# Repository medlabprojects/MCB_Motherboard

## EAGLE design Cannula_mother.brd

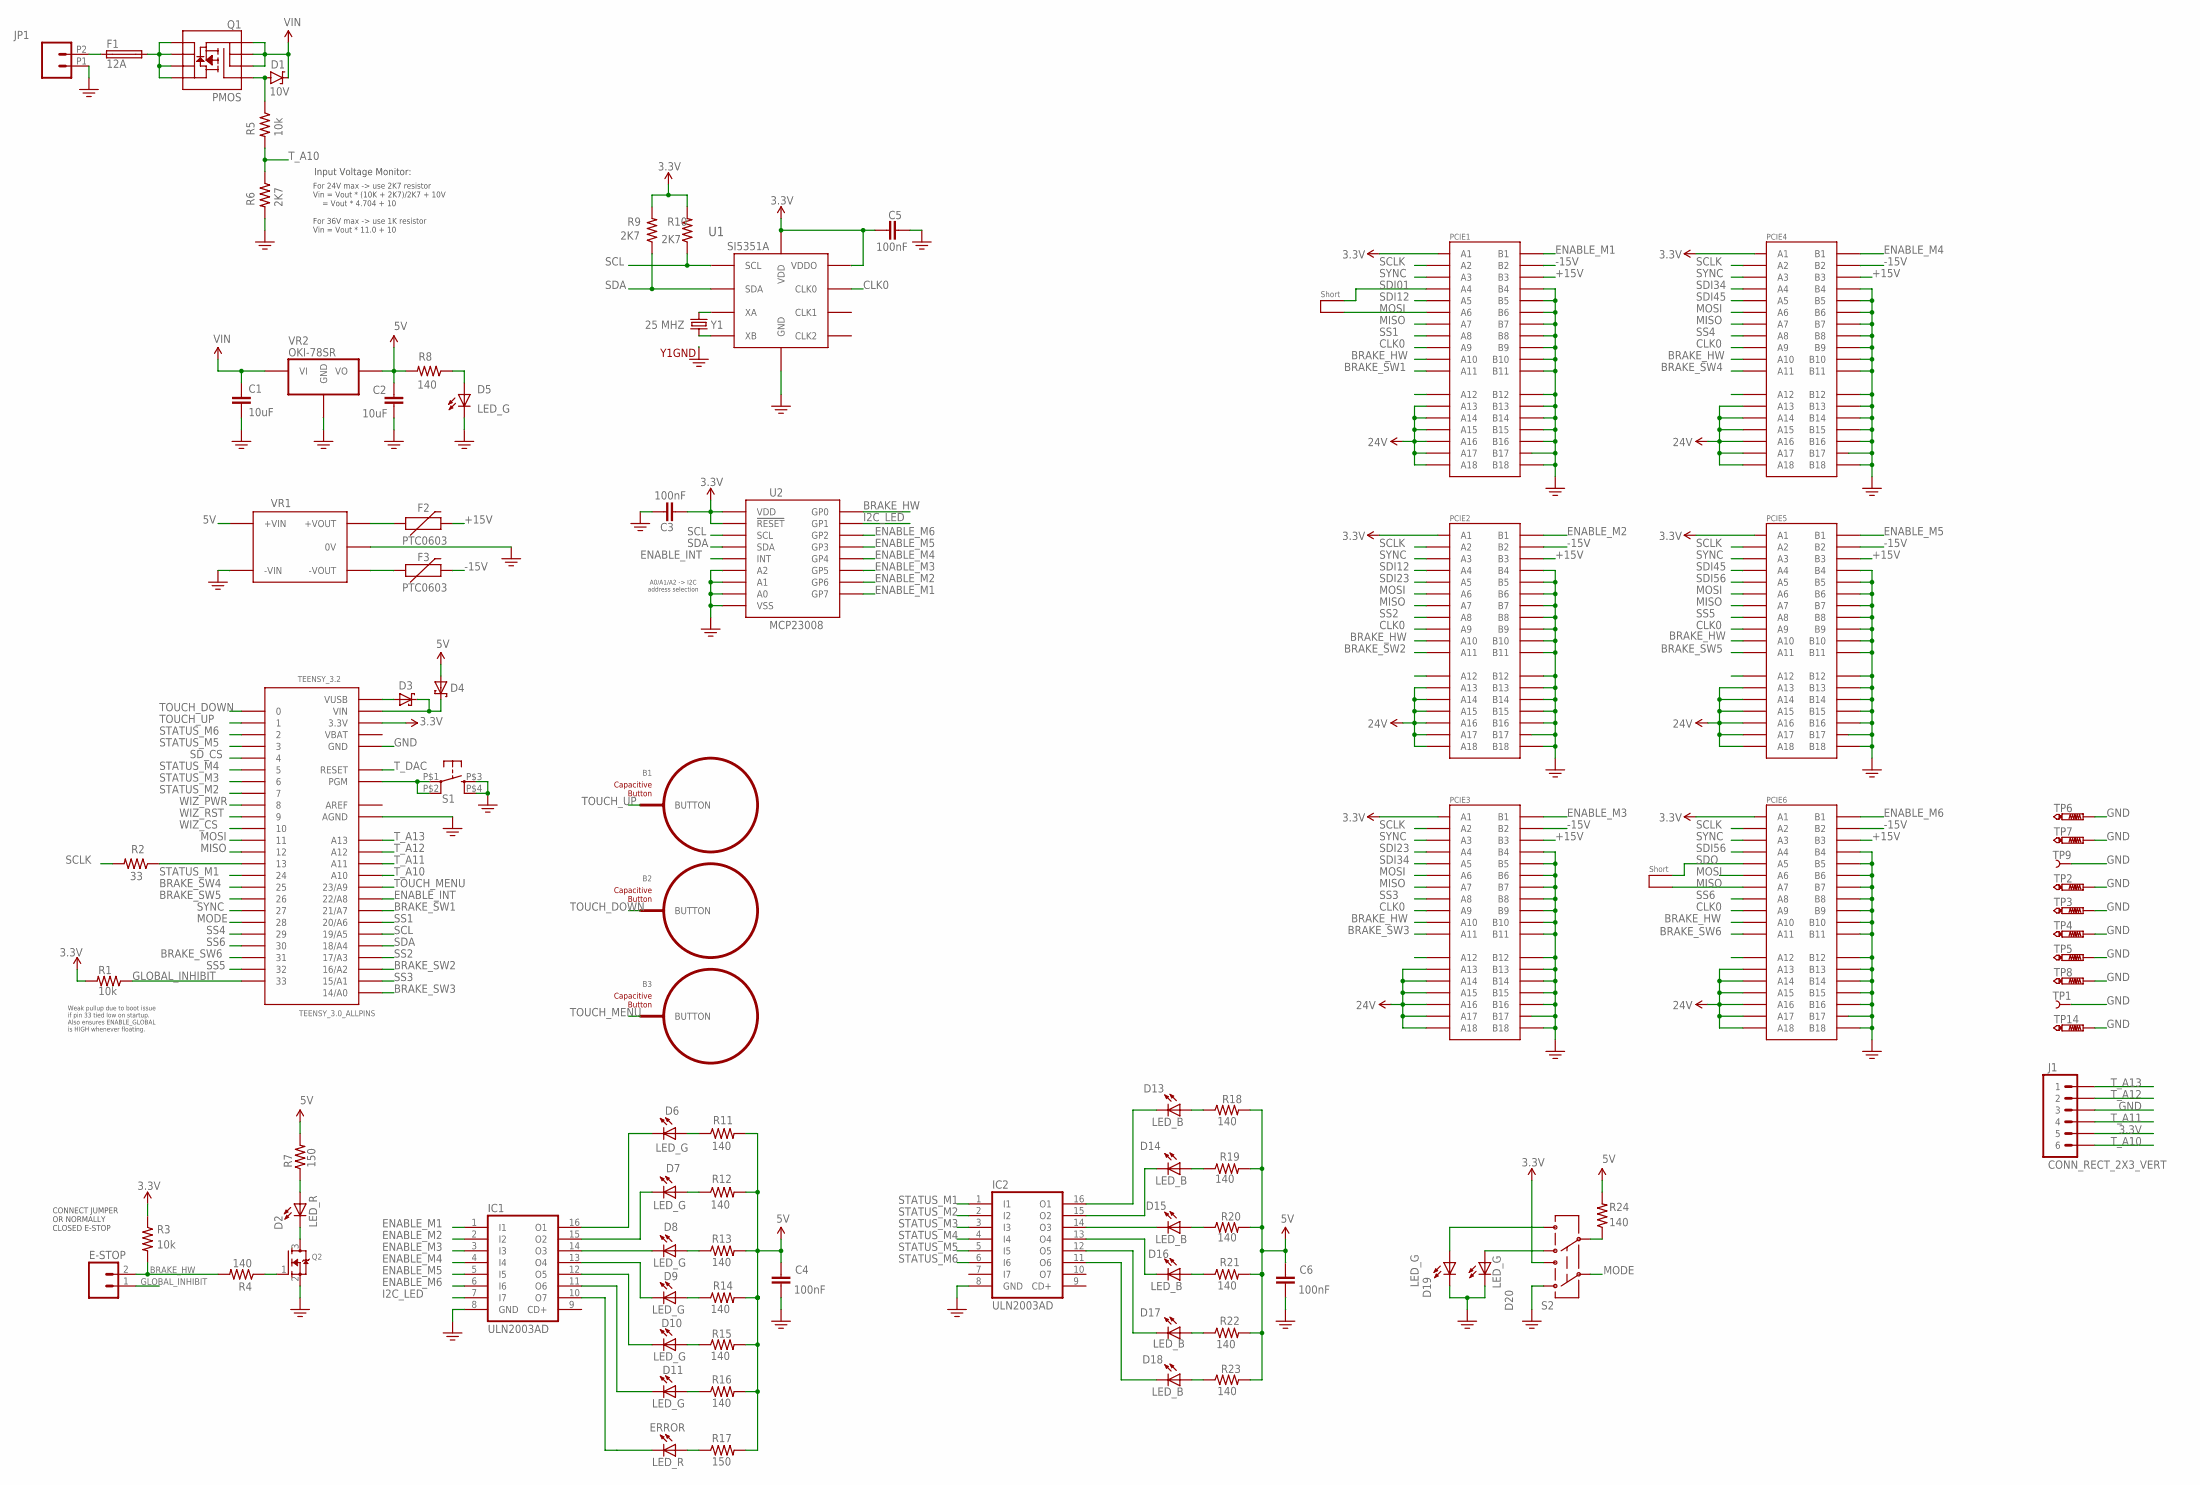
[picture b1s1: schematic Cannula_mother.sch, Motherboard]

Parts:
B1, B2: BUTTON_PASSIVE-8MM-ARROW; BUTTON_PASSIVE_8MM_UP
B3: BUTTON_PASSIVE-8MM-MENU; BUTTON_PASSIVE_8MM_MENU
C1, C2: 10uF; 1210
C3, C4, C5, C6: 100nF; 0603-CAP
D1: 10V; SOD-323
D2: LED_R; LED-0805
D3, D4: DIODE-POWERDI123; POWERDI123
D5, D6, D7, D8, D9, D10, D11, D19, D20: LED_G; LED-0805
D13, D14, D15, D16, D17, D18: LED_B; LED-0805
E-STOP: M02LOCK; 1X02_LOCK
ERROR: LED_R; LED-0805
F1: 12A; 1206
F2, F3: PTC0603; 0603
IC1, IC2: ULN2003AD; SO16
J1: CONN_RECT_2X3_VERT; 2X3
JP1: M026.35MM_SCREWTERM; 1X02_6.35_SCREWTERM
JP3, JP4: SHORT
PCIE1, PCIE2, PCIE3, PCIE4, PCIE5, PCIE6: PCIE-36-SKT
Q1: PMOS; SO08
Q2: MOSFET-NREFLOW; SOT23
R1, R3, R5: 10k; 0603-RES
R2: 33; 0603-RES
R4, R8, R11, R12, R13, R14, R15, R16, R18, R19, R20, R21, R22, R23, R24: 140; 0603-RES
R6, R9, R10: 2K7; 0603-RES
R7, R17: 150; 0603-RES
S1: SWITCH-TACT; LS38
S2: SWITCH-DPDT-SLIDER-SMD; JS202011SCQN
TEENSY_3.2: TEENSY_3.0_ALLPINS
TP1, TP9: TEST-POINT_5021
TP2, TP3, TP4, TP5, TP6, TP7, TP8, TP14: PTR1TP20R; TP20R
U1: SI5351A; MSOP10
U2: MCP23008; SSOP20
VR1: DCDC_IA_SERIES0515S; DCDC_IA_SERIES
VR2: OKI-78SR
Y1: 25 MHZ; CX3225SB

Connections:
3.3V: C3.1, C5.1, J1.5, PCIE1.A1, PCIE2.A1, PCIE3.A1, PCIE4.A1, PCIE5.A1, PCIE6.A1, R1.2, R3.1, R9.2, R10.2, S2.3, TEENSY_3.2.3.3V, TEENSY_3.2.3.3V1 (3.3V), TEENSY_3.2.3.3V2 (3.3V), U1.1 (VDD), U1.7 (VDDO), U2.6 (!RESET), U2.20 (VDD)
5V: C2.1, C4.1, C6.1, D4.P$2 (A), R7.2, R8.2, R11.2, R12.2, R13.2, R14.2, R15.2, R16.2, R17.2, R18.2, R19.2, R20.2, R21.2, R22.2, R23.2, R24.2, VR1.+VIN, VR2.P$3 (VO)
+15V: F2.2, PCIE1.B3, PCIE2.B3, PCIE3.B3, PCIE4.B3, PCIE5.B3, PCIE6.B3
-15V: F3.2, PCIE1.B2, PCIE2.B2, PCIE3.B2, PCIE4.B2, PCIE5.B2, PCIE6.B2
AREF: TEENSY_3.2.AREF
B: Q2.1 (G), R4.1
BRAKE_HW: E-STOP.2, PCIE1.A10, PCIE2.A10, PCIE3.A10, PCIE4.A10, PCIE5.A10, PCIE6.A10, R3.2, R4.2, U2.12 (GP0)
BRAKE_SW1: PCIE1.A11, TEENSY_3.2.21/A7
BRAKE_SW2: PCIE2.A11, TEENSY_3.2.16/A2
BRAKE_SW3: PCIE3.A11, TEENSY_3.2.14/A0
BRAKE_SW4: PCIE4.A11, TEENSY_3.2.25
BRAKE_SW5: PCIE5.A11, TEENSY_3.2.26
BRAKE_SW6: PCIE6.A11, TEENSY_3.2.31
C: D2.C, Q2.3 (D)
CLK0: PCIE1.A9, PCIE2.A9, PCIE3.A9, PCIE4.A9, PCIE5.A9, PCIE6.A9, U1.10 (CLK0)
ENABLE_INT: TEENSY_3.2.22/A8, U2.8 (INT)
ENABLE_M1: IC1.1 (I1), PCIE1.B1, U2.19 (GP7)
ENABLE_M2: IC1.2 (I2), PCIE2.B1, U2.18 (GP6)
ENABLE_M3: IC1.3 (I3), PCIE3.B1, U2.17 (GP5)
ENABLE_M4: IC1.4 (I4), PCIE4.B1, U2.16 (GP4)
ENABLE_M5: IC1.5 (I5), PCIE5.B1, U2.15 (GP3)
ENABLE_M6: IC1.6 (I6), PCIE6.B1, U2.14 (GP2)
GLOBAL_INHIBIT: E-STOP.1, R1.1, TEENSY_3.2.33
GND: C1.2, C2.2, C3.2, C4.2, C5.2, C6.2, D5.C, D19.C, D20.C, IC1.8 (GND), IC2.8 (GND), J1.3, JP1.P1 (1), PCIE1.B4, PCIE1.B5, PCIE1.B6, PCIE1.B7, PCIE1.B8, PCIE1.B9, PCIE1.B10, PCIE1.B11, PCIE1.B12, PCIE1.B13, PCIE1.B14, PCIE1.B15, PCIE1.B16, PCIE1.B17, PCIE1.B18, PCIE2.B4, PCIE2.B5, PCIE2.B6, PCIE2.B7, PCIE2.B8, PCIE2.B9, PCIE2.B10, PCIE2.B11, PCIE2.B12, PCIE2.B13, PCIE2.B14, PCIE2.B15, PCIE2.B16, PCIE2.B17, PCIE2.B18, PCIE3.B4, PCIE3.B5, PCIE3.B6, PCIE3.B7, PCIE3.B8, PCIE3.B9, PCIE3.B10, PCIE3.B11, PCIE3.B12, PCIE3.B13, PCIE3.B14, PCIE3.B15, PCIE3.B16, PCIE3.B17, PCIE3.B18, PCIE4.B4, PCIE4.B5, PCIE4.B6, PCIE4.B7, PCIE4.B8, PCIE4.B9, PCIE4.B10, PCIE4.B11, PCIE4.B12, PCIE4.B13, PCIE4.B14, PCIE4.B15, PCIE4.B16, PCIE4.B17, PCIE4.B18, PCIE5.B4, PCIE5.B5, PCIE5.B6, PCIE5.B7, PCIE5.B8, PCIE5.B9, PCIE5.B10, PCIE5.B11, PCIE5.B12, PCIE5.B13, PCIE5.B14, PCIE5.B15, PCIE5.B16, PCIE5.B17, PCIE5.B18, PCIE6.B4, PCIE6.B5, PCIE6.B6, PCIE6.B7, PCIE6.B8, PCIE6.B9, PCIE6.B10, PCIE6.B11, PCIE6.B12, PCIE6.B13, PCIE6.B14, PCIE6.B15, PCIE6.B16, PCIE6.B17, PCIE6.B18, Q2.2 (S), R6.2, S1.P$3 (3), S1.P$4 (4), S2.1, TEENSY_3.2.AGND, TEENSY_3.2.GND, TEENSY_3.2.GND1 (GND), TEENSY_3.2.GND2 (GND), TP1.P$1, TP2.TP, TP3.TP, TP4.TP, TP5.TP, TP6.TP, TP7.TP, TP8.TP, TP9.P$1, TP14.TP, U1.8 (GND), U2.3 (A2), U2.4 (A1), U2.5 (A0), U2.9 (VSS), VR1.0V, VR1.-VIN, VR2.P$2 (GND), Y1.GND@1 (GND), Y1.GND@2 (GND)
I2C_LED: IC1.7 (I7), U2.13 (GP1)
MISO: JP4.P$2, PCIE1.A7, PCIE2.A7, PCIE3.A7, PCIE4.A7, PCIE5.A7, PCIE6.A7, TEENSY_3.2.12
MODE: S2.2, TEENSY_3.2.28
MOSI: JP3.P$2, PCIE1.A6, PCIE2.A6, PCIE3.A6, PCIE4.A6, PCIE5.A6, PCIE6.A6, TEENSY_3.2.11
unnamed: F2.1, VR1.+VOUT
unnamed: F3.1, VR1.-VOUT
unnamed: D8.C, IC1.14 (O3)
unnamed: D2.A, R7.1
unnamed: D1.A, Q1.4 (G), R5.1
unnamed: D15.C, IC2.14 (O3)
unnamed: F1.P$2 (2), Q1.5 (D), Q1.6 (D), Q1.7 (D), Q1.8 (D)
unnamed: D5.A, R8.1
unnamed: R24.1, S2.5
unnamed: D20.A, S2.4
unnamed: D19.A, S2.6
unnamed: ERROR.A, R17.1
unnamed: F1.P$1 (1), JP1.P2 (2)
unnamed: D17.A, R22.1
unnamed: D13.A, R18.1
unnamed: D14.A, R19.1
unnamed: D15.A, R20.1
unnamed: D16.A, R21.1
unnamed: D18.A, R23.1
unnamed: ERROR.C, IC1.10 (O7)
unnamed: D10.A, R15.1
unnamed: D6.A, R11.1
unnamed: D7.A, R12.1
unnamed: D8.A, R13.1
unnamed: D9.A, R14.1
unnamed: D11.A, R16.1
unnamed: D13.C, IC2.16 (O1)
unnamed: D14.C, IC2.15 (O2)
unnamed: D16.C, IC2.13 (O4)
unnamed: D17.C, IC2.12 (O5)
unnamed: D18.C, IC2.11 (O6)
unnamed: D7.C, IC1.15 (O2)
unnamed: D9.C, IC1.13 (O4)
unnamed: D10.C, IC1.12 (O5)
unnamed: D11.C, IC1.11 (O6)
unnamed: D6.C, IC1.16 (O1)
unnamed: R2.1, TEENSY_3.2.13
PGM: S1.P$1 (1), S1.P$2 (2), TEENSY_3.2.PGM
SCL: R10.1, TEENSY_3.2.19/A5, U1.4 (SCL), U2.1 (SCL)
SCLK: PCIE1.A2, PCIE2.A2, PCIE3.A2, PCIE4.A2, PCIE5.A2, PCIE6.A2, R2.2
SDA: R9.1, TEENSY_3.2.18/A4, U1.5 (SDA), U2.2 (SDA)
SDI01: JP3.P$1, PCIE1.A4
SDI12: PCIE1.A5, PCIE2.A4
SDI23: PCIE2.A5, PCIE3.A4
SDI34: PCIE3.A5, PCIE4.A4
SDI45: PCIE4.A5, PCIE5.A4
SDI56: PCIE5.A5, PCIE6.A4
SDO: JP4.P$1, PCIE6.A5
SD_CS: TEENSY_3.2.4
SS1: PCIE1.A8, TEENSY_3.2.20/A6
SS2: PCIE2.A8, TEENSY_3.2.17/A3
SS3: PCIE3.A8, TEENSY_3.2.15/A1
SS4: PCIE4.A8, TEENSY_3.2.29
SS5: PCIE5.A8, TEENSY_3.2.32
SS6: PCIE6.A8, TEENSY_3.2.30
STATUS_M1: IC2.1 (I1), TEENSY_3.2.24
STATUS_M2: IC2.2 (I2), TEENSY_3.2.7
STATUS_M3: IC2.3 (I3), TEENSY_3.2.6
STATUS_M4: IC2.4 (I4), TEENSY_3.2.5
STATUS_M5: IC2.5 (I5), TEENSY_3.2.3
STATUS_M6: IC2.6 (I6), TEENSY_3.2.2
SYNC: PCIE1.A3, PCIE2.A3, PCIE3.A3, PCIE4.A3, PCIE5.A3, PCIE6.A3, TEENSY_3.2.27
TOUCH_DOWN: B2.BUTTON, TEENSY_3.2.0
TOUCH_MENU: B3.BUTTON, TEENSY_3.2.23/A9
TOUCH_UP: B1.BUTTON, TEENSY_3.2.1
T_A10: J1.6, R5.2, R6.1, TEENSY_3.2.A10
T_A11: J1.4, TEENSY_3.2.A11
T_A12: J1.2, TEENSY_3.2.A12
T_A13: J1.1, TEENSY_3.2.A13
T_DAC: TEENSY_3.2.RESET
T_VIN: D3.P$1 (C), D4.P$1 (C), TEENSY_3.2.VIN
VBAT: TEENSY_3.2.VBAT
VIN: C1.1, D1.C, PCIE1.A13, PCIE1.A14, PCIE1.A15, PCIE1.A16, PCIE1.A17, PCIE1.A18, PCIE2.A13, PCIE2.A14, PCIE2.A15, PCIE2.A16, PCIE2.A17, PCIE2.A18, PCIE3.A13, PCIE3.A14, PCIE3.A15, PCIE3.A16, PCIE3.A17, PCIE3.A18, PCIE4.A13, PCIE4.A14, PCIE4.A15, PCIE4.A16, PCIE4.A17, PCIE4.A18, PCIE5.A13, PCIE5.A14, PCIE5.A15, PCIE5.A16, PCIE5.A17, PCIE5.A18, PCIE6.A13, PCIE6.A14, PCIE6.A15, PCIE6.A16, PCIE6.A17, PCIE6.A18, Q1.1 (S), Q1.2 (S), Q1.3 (S), VR2.P$1 (VI)
VUSB: D3.P$2 (A), TEENSY_3.2.VUSB
WIZ_CS: TEENSY_3.2.10
WIZ_PWR: TEENSY_3.2.8
WIZ_RST: TEENSY_3.2.9
XA: U1.2 (XA), Y1.HOT2 (2)
XB: U1.3 (XB), Y1.HOT1 (1)

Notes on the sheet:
CONNECT JUMPER OR NORMALLY CLOSED E-STOP
A0/A1/A2 -> I2C address selection
Weak pullup due to boot issue if pin 33 tied low on startup. Also ensures ENABLE_GLOBAL is HIGH whenever floating.
Input Voltage Monitor:
For 24V max -> use 2K7 resistor Vin = Vout * (10K + 2K7)/2K7 + 10V = Vout * 4.704 + 10 For 36V max -> use 1K resistor Vin = Vout * 11.0 + 10

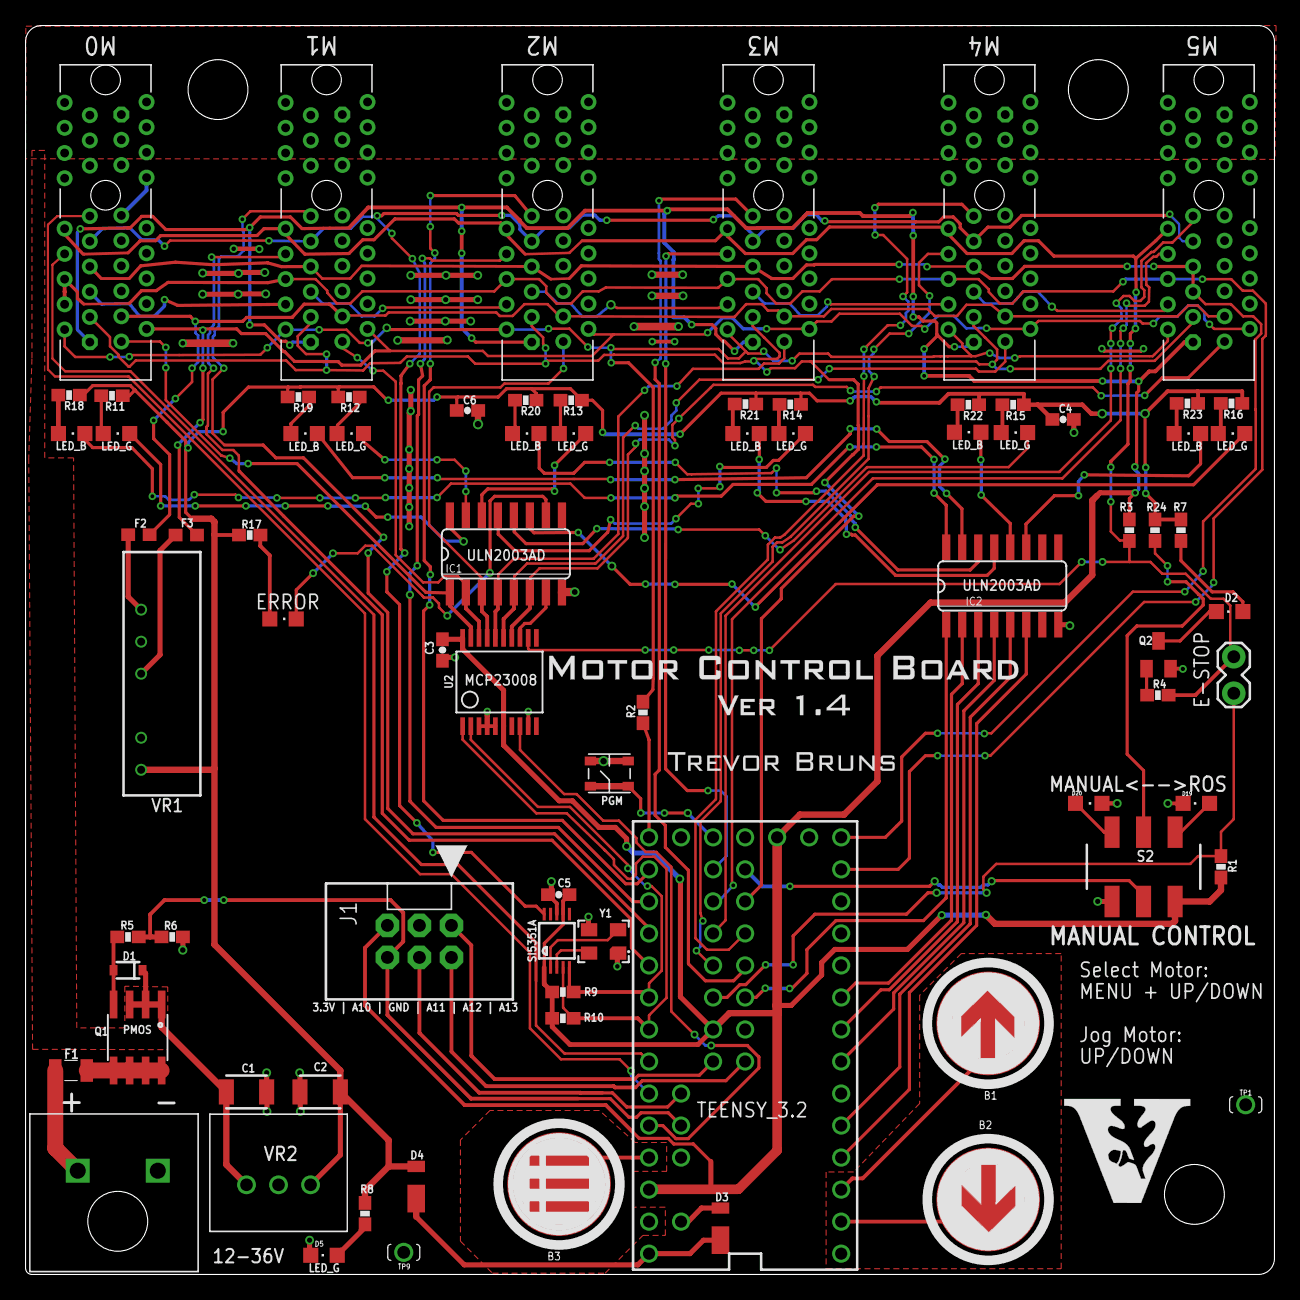
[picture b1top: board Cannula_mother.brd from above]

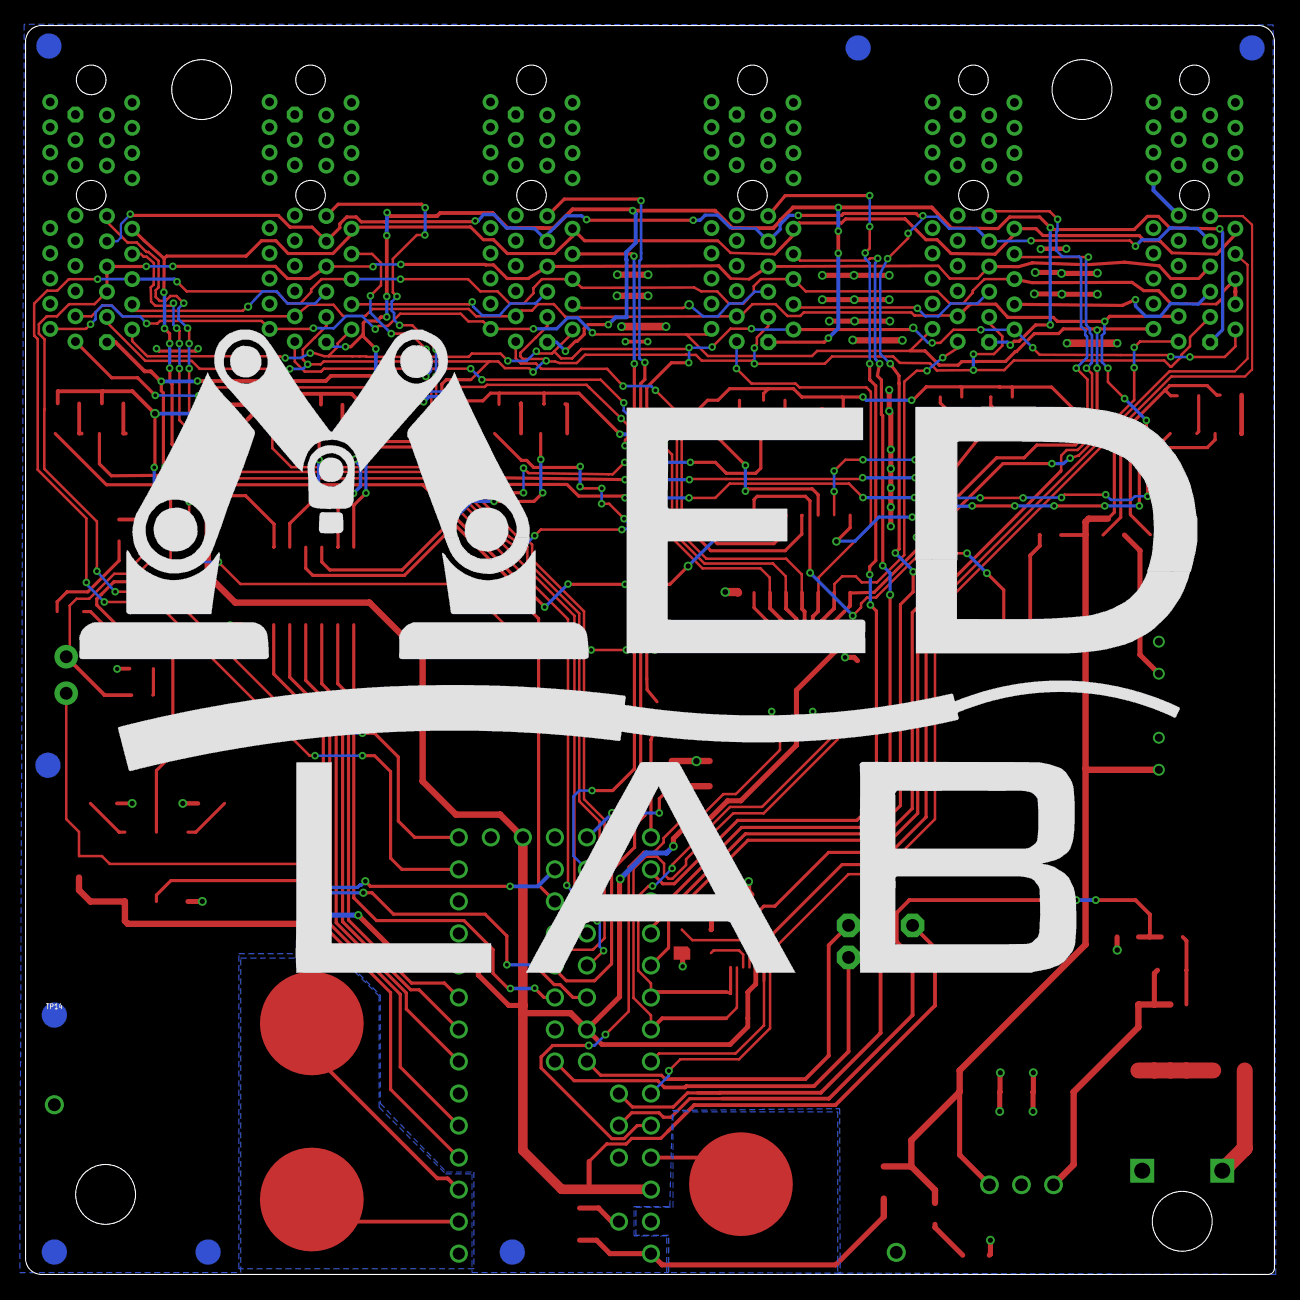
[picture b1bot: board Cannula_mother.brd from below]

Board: 2 copper layers, 99.1 x 99.1 mm, 96 parts (9 on the bottom side), 100 nets.

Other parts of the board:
24V: SPACER
U$1, U$3, U$4: SPACER
U$2: LOGO_MOTOR_CONTROL_1.4
U$6: LOGO_MEDLAB_3X2
U$8: LOGO_V_OAK

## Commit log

2018-11-02 1.4- as ordered
2018-11-03 Changes almost finished
2018-11-03 Finished edits
2018-11-04 Created gerbers

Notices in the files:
parts and their libraries:
Cannula_1_0: License : http://creativecommons.org/licenses/by-sa/3.1/ (Creative Commons 3.1)
SparkFun-Capacitors: Licensing: Creative Commons ShareAlike 4.0 International - https://creativecommons.org/licenses/by-sa/4.0
